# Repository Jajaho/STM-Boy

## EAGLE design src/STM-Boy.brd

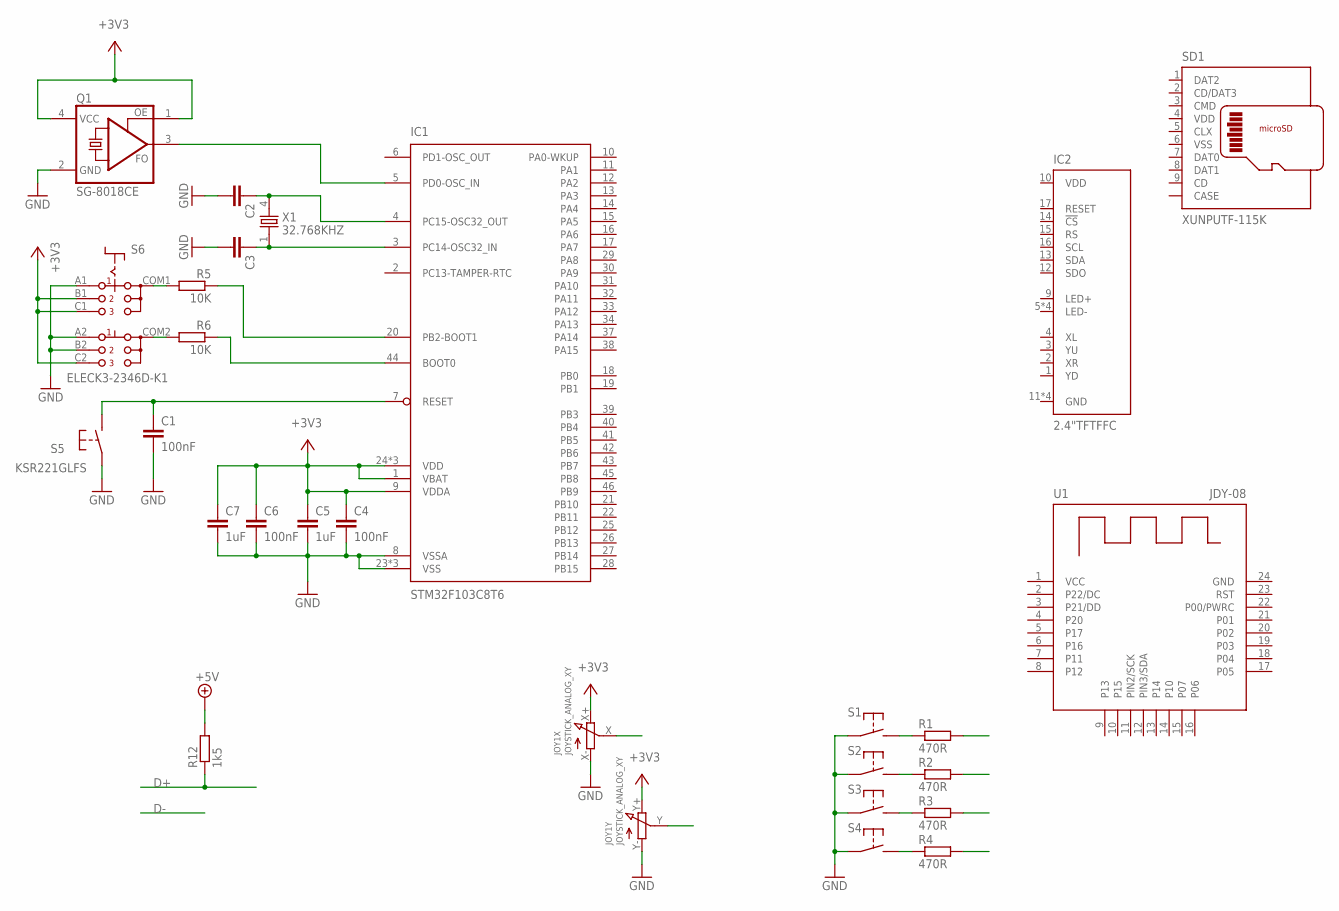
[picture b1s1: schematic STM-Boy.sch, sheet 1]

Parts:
C1, C4, C6: 100nF; C0805
C2, C3: C-EUC0805; C0805
C5, C7: 1uF; C0805
IC1: STM32F103C8T6; LQFP48
IC2: 2.4"TFTFFC; FPC_18
JOY1: JOYSTICK_ANALOG_XY; JOYSTICK_ANALOG_MINITHM
Q1: SG-8018CE; SMD-3225
R1, R2, R3, R4: 470R; R0805
R5, R6: 10K; R0805
R12: 1k5; R0805
S1, S2, S3, S4: 8MM_SOFT_BUTTON; 8MM_BUTTON
S5: KSR221GLFS; KSR211GLFS
S6: ELECK3-2346D-K1
SD1: XUNPUTF-115K
U1: JDY-08
X1: 32.768KHZ; SMD-6914

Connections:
+3V3: C4.1, C5.1, C6.1, C7.1, IC1.1 (VBAT), IC1.9 (VDDA), IC1.24 (VDD), IC1.36 (VDD), IC1.48 (VDD), JOY1.X+ (E), JOY1.Y+ (E), Q1.1 (OE), Q1.4 (VCC), S6.B1 (A2), S6.C1 (A3), S6.C2 (B3)
+5V: R12.2
D+: R12.1
GND: C1.2, C2.2, C3.2, C4.2, C5.2, C6.2, C7.2, IC1.8 (VSSA), IC1.23 (VSS), IC1.35 (VSS), IC1.47 (VSS), JOY1.X- (A), JOY1.Y- (A), Q1.2 (GND), S1.1, S1.2 (1), S2.1, S2.2 (1), S3.1, S3.2 (1), S4.1, S4.2 (1), S5.1, S6.A1, S6.A2 (B1), S6.B2; also elsewhere on the board
unnamed: C1.1, IC1.7 (RESET), S5.2 (S)
unnamed: R1.1, S1.3 (S), S1.4 (S)
unnamed: R2.1, S2.3 (S), S2.4 (S)
unnamed: R3.1, S3.3 (S), S3.4 (S)
unnamed: R4.1, S4.3 (S), S4.4 (S)
unnamed: IC1.5 (PD0-OSC_IN), Q1.3 (FO)
unnamed: IC1.20 (PB2-BOOT1), R5.1
unnamed: R5.2, S6.COM1 (A)
unnamed: R6.2, S6.COM2 (B)
unnamed: C2.1, IC1.4 (PC15-OSC32_OUT), X1.4 (1)
unnamed: C3.1, IC1.3 (PC14-OSC32_IN), X1.1 (2)
unnamed: IC1.44 (BOOT0), R6.1

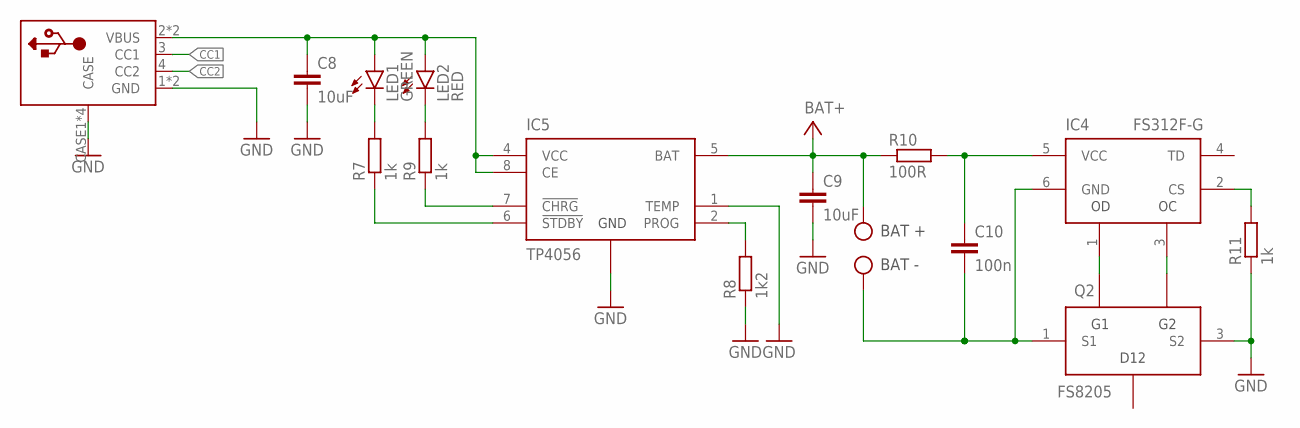
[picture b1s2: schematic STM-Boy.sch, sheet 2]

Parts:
C8, C9: 10uF; C0805
C10: 100n; C0805
IC4: FS312F-G; SOT-23-6
IC5: TP4056; SOP-8
J1: USB-C_CON; USB-C6PIN
J4: BAT +; CON-PAD
J5: BAT -; CON-PAD
LED1: GREEN; CHIPLED_0603
LED2: RED; CHIPLED_0603
Q2: FS8205; SOT-23-6
R7, R9, R11: 1k; R0805
R8: 1k2; R0805
R10: 100R; R0805

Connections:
BAT+: C9.1, IC5.5 (BAT), J4.1, R10.1
BAT-: C10.2, IC4.6 (GND), J5.1, Q2.1 (S1)
CC1: J1.3 (CC1)
CC2: J1.4 (CC2)
GND: C8.2, C9.2, IC5.1 (TEMP), IC5.3 (GND), IC5.9 (GND), J1.1 (GND), J1.6 (GND), J1.CASE1 (CASE), J1.CASE2 (CASE), J1.CASE3 (CASE), J1.CASE4 (CASE), Q2.3 (S2), R8.1, R11.1; also elsewhere on the board
unnamed: LED1.C, R7.2
unnamed: LED2.C, R9.2
unnamed: IC5.2 (PROG), R8.2
unnamed: IC5.7 (!CHRG), R9.1
unnamed: IC5.6 (!STDBY), R7.1
unnamed: IC4.1 (OD), Q2.6 (G1)
unnamed: IC4.3 (OC), Q2.4 (G2)
unnamed: IC4.2 (CS), R11.2
unnamed: C10.1, IC4.5 (VCC), R10.2
VBUS: C8.1, IC5.4 (VCC), IC5.8 (CE), J1.2 (VBUS), J1.5 (VBUS), LED1.A, LED2.A

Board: 2 copper layers, 43 parts (36 on the bottom side), 26 nets, no tracks yet.

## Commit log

2023-07-04 Adds old project files
